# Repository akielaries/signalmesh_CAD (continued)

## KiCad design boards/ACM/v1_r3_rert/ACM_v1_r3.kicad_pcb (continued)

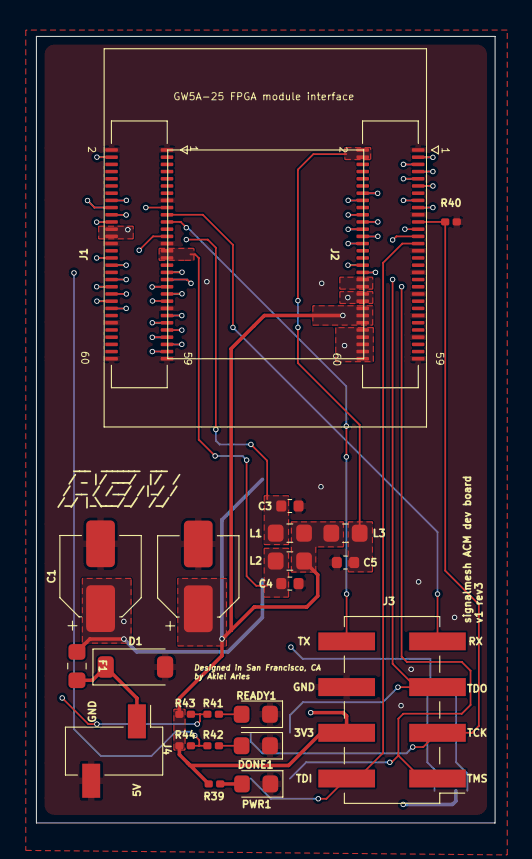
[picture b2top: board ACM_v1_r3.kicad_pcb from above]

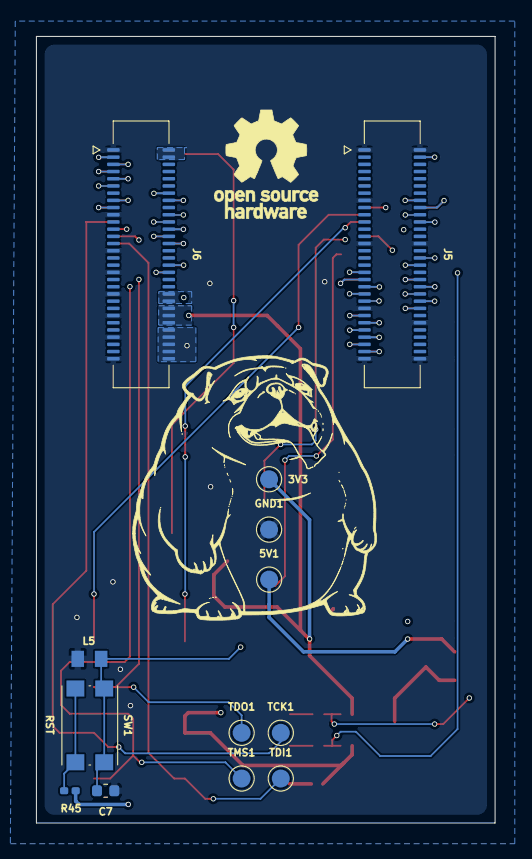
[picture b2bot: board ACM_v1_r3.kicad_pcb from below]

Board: 4 copper layers, 25.5 x 43.7 mm, 36 parts (13 on the bottom side), 66 nets.

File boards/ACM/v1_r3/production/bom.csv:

Designator,Footprint,Quantity,Value,LCSC Part #
"3V3, 5V1, GND1, TCK1, TDI1, TDO1, TMS1",TestPoint_Pad_D1.0mm,7,TestPoint,
"C1, C2",CP_Elec_4x3,2,220uF 10V,
"C3, C4, C5, C7",0402,4,100nF,
D1,D_SOD-123,1,20V 3A,
"DONE1, PWR1, READY1",0603,3,GREEN_LED,
F1,0603,1,6V 2A,
"J1, J2, J5, J6",Hirose_DF40C-60DS-0.4V_2x30_P0.4mm,4,DF40C-60DS-0.4V(51),
J3,PinHeader_2x04_P2.54mm_Vertical_SMD,1,Conn_02x04_Odd_Even,
J4,PinSocket_1x02_P2.54mm_Vertical_SMD_Pin1Left,1,Conn_01x02,
"L1, L2, L3",0603,3,PZ1608D300-3R0TF,
L5,INDC1005X45,1,LXES15AAA1-153,
"R39, R41, R42",0201,3,4.7k,
R40,0201,1,5.1K,
"R43, R44",0201,2,49.9k,
R45,0201,1,100R,
SW1,SW_Push_1P1T_NO_CK_KMR2,1,RST,

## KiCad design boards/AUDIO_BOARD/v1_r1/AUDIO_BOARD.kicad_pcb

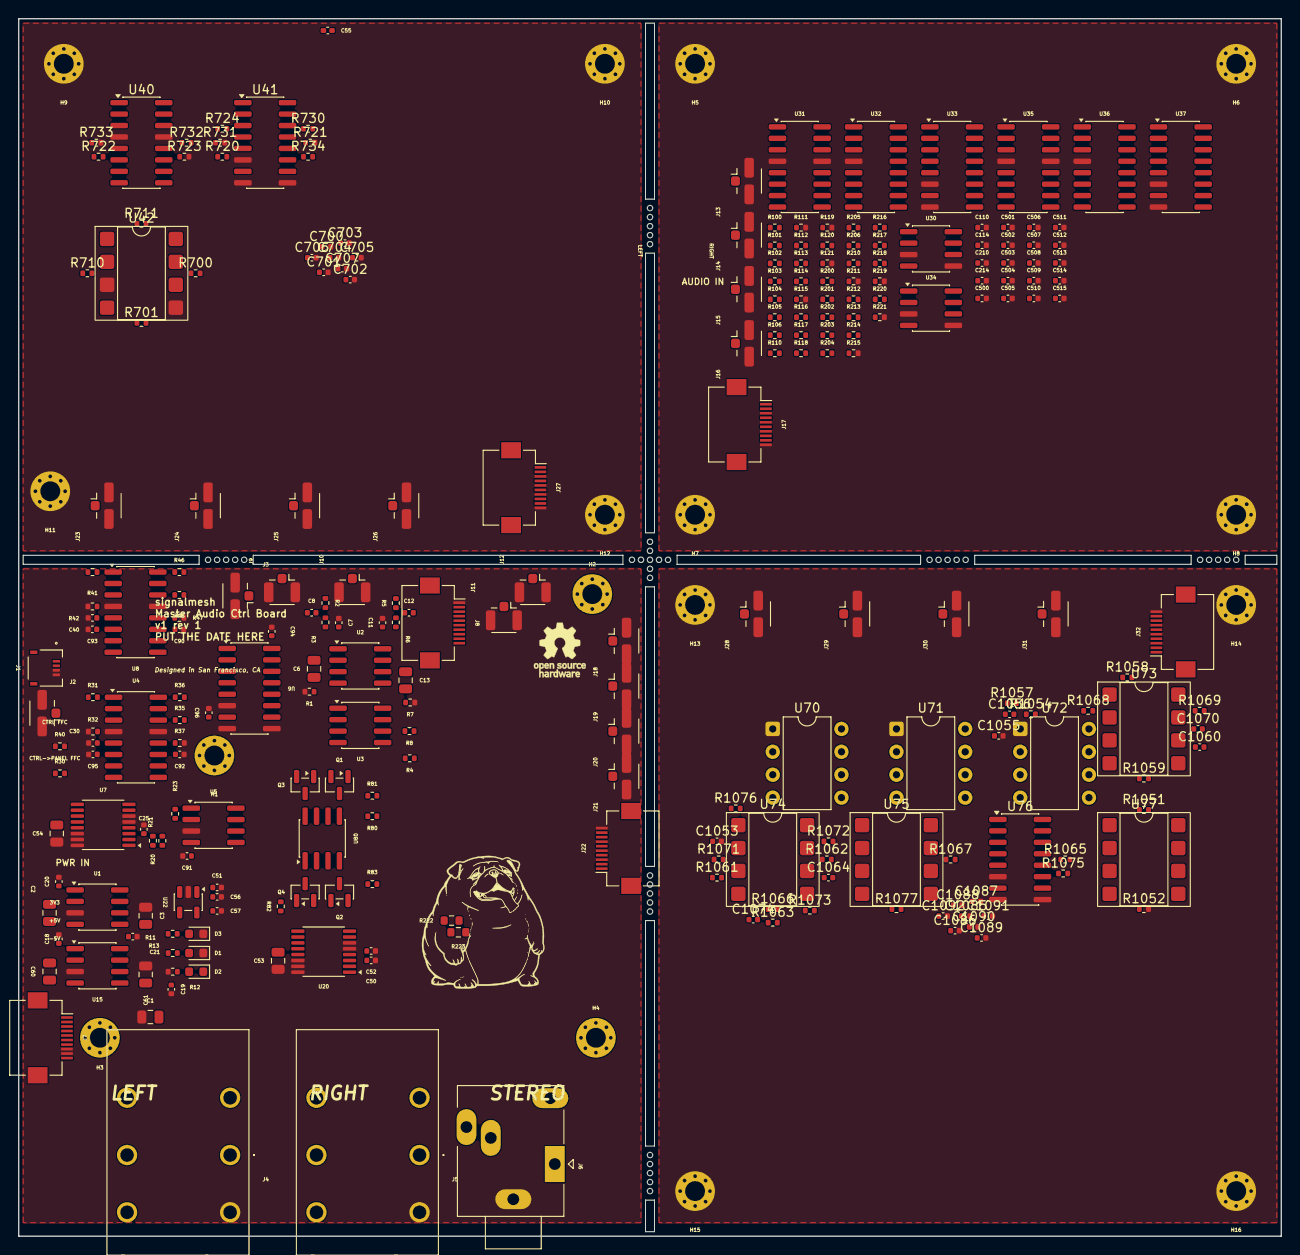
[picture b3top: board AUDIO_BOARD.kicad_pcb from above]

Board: 4 copper layers, 140.0 x 135.0 mm, 266 parts (0 on the bottom side), 170 nets, no tracks yet.

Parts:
C1, C2, C3, C53, C54: 10uF; C_0805_2012Metric
C6, C13, C60: 1uF; C_0805_2012Metric
C7, C11: 560pF; C_0402_1005Metric
C8, C12, C30, C40, C110, C114, C210, C214, C1060, C1064, C1070, C1074: 1nF; C_0402_1005Metric
C18, C19, C20, C21, C51, C52, C55, C90, C91, C92, C93, C94, C95, C96, C500, C501, C502, C503, C504, C505, C506, C507, C508, C509, C510, C511, C512, C513, C514, C515, C700, C701, C702, C703, C704, C705, C706, C707, C1085, C1086, C1087, C1088, C1089, C1090, C1091, C1092: 100nF; C_0402_1005Metric
C25, C50, C56, C57: 1uF; C_0402_1005Metric
C61: 22uF; C_0805_2012Metric
C1053: 10uF; C_0402_1005Metric
C1055, C1056: 100pF; C_0402_1005Metric
D1, D2, D3: LED; LED_0603_1608Metric
H1, H2, H3, H4, H5, H6, H7, H8, H9, H10, H11, H12, H13, H14, H15, H16: M2; MountingHole_2.2mm_M2_Pad_Via
J1: PWR FFC 4p; AMPHENOL_F3311A7H121004E200
J2: U.FL L in; U.FL_Hirose_U.FL-R-SMT-1_Vertical
J3: U.FL R in; U.FL_Hirose_U.FL-R-SMT-1_Vertical
J4: 1/4in L; ACJSMHOM
J5: 1/4in R; ACJSMHOM
J6: 3.5mm HP; Jack_3.5mm_Ledino_KB3SPRS_Horizontal
J7: CTRL FFC; Hirose_FH12-10S-0.5SH_1x10-1MP_P0.50mm_Horizontal
J8: CTRL->PANEL FFC; Hirose_FH12-10S-0.5SH_1x10-1MP_P0.50mm_Horizontal
J9: U.FL FX send L; U.FL_Hirose_U.FL-R-SMT-1_Vertical
J10: U.FL FX send R; U.FL_Hirose_U.FL-R-SMT-1_Vertical
J11: U.FL FX return L; U.FL_Hirose_U.FL-R-SMT-1_Vertical
J12: U.FL FX return R; U.FL_Hirose_U.FL-R-SMT-1_Vertical
J13: U.FL AUDIO L IN; U.FL_Hirose_U.FL-R-SMT-1_Vertical
J14: U.FL AUDIO R IN; U.FL_Hirose_U.FL-R-SMT-1_Vertical
J15: U.FL AUDIO L OUT; U.FL_Hirose_U.FL-R-SMT-1_Vertical
J16: U.FL AUDIO R OUT; U.FL_Hirose_U.FL-R-SMT-1_Vertical
J17: FILTER FFC; Hirose_FH12-10S-0.5SH_1x10-1MP_P0.50mm_Horizontal
J18: U.FL->FILT L IN; U.FL_Hirose_U.FL-R-SMT-1_Vertical
J19: U.FL->FILT R IN; U.FL_Hirose_U.FL-R-SMT-1_Vertical
J20: U.FL<-FILT L OUT; U.FL_Hirose_U.FL-R-SMT-1_Vertical
J21: U.FL<-FILT R OUT; U.FL_Hirose_U.FL-R-SMT-1_Vertical
J22: FILTER-IF FFC; Hirose_FH12-10S-0.5SH_1x10-1MP_P0.50mm_Horizontal
J23: FX-A L IN; U.FL_Hirose_U.FL-R-SMT-1_Vertical
J24: FX-A R IN; U.FL_Hirose_U.FL-R-SMT-1_Vertical
J25: FX-A L OUT; U.FL_Hirose_U.FL-R-SMT-1_Vertical
J26: FX-A R OUT; U.FL_Hirose_U.FL-R-SMT-1_Vertical
J27: FX-A CTRL; Hirose_FH12-10S-0.5SH_1x10-1MP_P0.50mm_Horizontal
J28: FX-B L IN; U.FL_Hirose_U.FL-R-SMT-1_Vertical
J29: FX-B R IN; U.FL_Hirose_U.FL-R-SMT-1_Vertical
J30: FX-B L OUT; U.FL_Hirose_U.FL-R-SMT-1_Vertical
J31: FX-B R OUT; U.FL_Hirose_U.FL-R-SMT-1_Vertical
J32: FX-B CTRL; Hirose_FH12-10S-0.5SH_1x10-1MP_P0.50mm_Horizontal
Q1, Q3: MMBT3904; SOT-23
Q2, Q4: MMBT3906; SOT-23
R1, R7, R20, R21, R23, R31, R36, R41, R46, R100, R101, R102, R103, R104, R105, R106, R112, R116, R120, R200, R201, R202, R203, R204, R205, R206, R212, R216, R220, R722, R732, R1051, R1052: 100k; R_0402_1005Metric
R2, R3, R5, R6, R113, R117, R213, R217, R724, R734, R1058, R1059, R1061, R1062, R1063, R1068, R1069, R1071, R1072, R1073: 10k; R_0402_1005Metric
R4, R8, R80, R82: 100R; R_0402_1005Metric
R11, R12, R13: 1k; R_0402_1005Metric
R30, R35, R40, R45: 20k; R_0402_1005Metric
R32, R37, R42, R47, R121, R221, R701, R711, R723, R733, R1054: 47k; R_0402_1005Metric
R81, R83: 22R; R_0402_1005Metric
R110, R114, R118, R210, R214, R218, R720, R730, R1065, R1066, R1067, R1075, R1076, R1077: 22k; R_0402_1005Metric
R111, R115, R119, R211, R215, R219, R721, R731: 220R; R_0402_1005Metric
R222, R223: 0; R_0603_1608Metric
R700, R710: 4k7; R_0402_1005Metric
R1057: 220k; R_0402_1005Metric
U1, U15: LTC660; SOIC-8_3.9x4.9mm_P1.27mm
U2, U3, U5, U30, U34, U80: OPA1678; SOIC-8_3.9x4.9mm_P1.27mm
U4, U8, U31, U32, U35, U36, U40: LM13700; SOIC-16_3.9x9.9mm_P1.27mm
U6, U41, U76: 4053; SOIC-16_3.9x9.9mm_P1.27mm
U7, U20: DAC8565; TSSOP-16_4.4x5mm_P0.65mm
U22: AP2112K-3.3; SOT-23-5
U33, U37: 4052; SOIC-16_3.9x9.9mm_P1.27mm
U42, U73, U74, U75, U77: OPA1678; DIP-8_W7.62mm_SMDSocket_SmallPads
U70, U71: MN3207; DIP-8_W7.62mm
U72: MN3101; DIP-8_W7.62mm

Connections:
+3V3: C55.1, C57.1, J8.8, R13.1, U22.5 (VOUT)
+5V: C1.1, C18.1, C20.1, C51.1, C52.1, C53.1, C54.1, C56.1, C90.1, C92.1, C94.1, J1.1, J1.2, J22.1, Q1.3 (C), Q3.3 (C), R11.1, U1.1 (BOOST), U1.8 (V+), U2.8 (V+), U3.8 (V+), U4.11 (V+), U5.8 (V+), U6.16 (VDD), U7.4 (AVDD), U7.12 (IOVDD), U7.13 (~RST), U8.11 (V+), U15.1 (BOOST), U15.8 (V+), U20.4 (AVDD), U20.12 (IOVDD), U20.13 (~RST), U22.1 (VIN), U22.3 (EN), U80.8 (V+)
-5V: C3.1, C19.1, C21.1, C61.1, C91.1, C93.1, C95.1, C96.1, D2.1 (K), J22.2, Q2.3 (C), Q4.3 (C), U1.5 (VOUT), U2.4 (V-), U3.4 (V-), U4.6 (V-), U5.4 (V-), U6.7 (VEE), U8.6 (V-), U15.5 (VOUT), U80.4 (V-)
/ANALOG_FILTER_CV/CV_CUTOFF: R20.2, U7.1 (VOUTA)
/ANALOG_FILTER_CV/CV_VCA: R36.2, R46.2, U7.7 (VOUTC)
/ANALOG_FILTER_CV/VCA_L_OUT: R37.1, U4.12, U6.13 (X1)
/ANALOG_FILTER_CV/VCA_R_OUT: R47.1, U6.1 (Y1), U8.12
/ANALOG_FILTER_CV/VCF_L_OUT: C30.1, R32.1, R35.1, U4.5
/ANALOG_FILTER_CV/VCF_R_OUT: C40.1, R42.1, R45.1, U8.5
/ANALOG_FILTER_CV/VCUTOFF: R23.2, R31.2, R41.2, U5.1
/ANALOG_FILTER_CV/VREF: C25.1, U7.3 (VREFH/VREFOUT)
/CS_DAC1: J7.4, U7.9 (~SYNC)
/CS_DAC2: J7.10, U20.9 (~SYNC)
/CS_POTS: J7.5, J8.5
/FILT_L_IN: R4.2, R30.2, U6.12 (X0)
/FILT_L_OUT: J9.1 (In), R222.2, U6.14 (X)
/FILT_R_IN: R8.2, R40.1, U6.2 (Y0)
/FILT_R_OUT: J10.1 (In), R223.2, U6.15 (Y)
/FX_CHAIN/DRV_L: R701.2, R720.1, R721.1, U41.12, U42.1
/FX_CHAIN/DRV_R: R711.2, R730.1, R731.1, U41.2, U42.7
/FX_CHAIN/TREM_L: R724.1, U40.8, U41.13
/FX_CHAIN/TREM_R: R734.1, U40.9, U41.1
/FX_CHORUS/AA_L: C1060.1, R1059.1, U70.3, U73.1
/FX_CHORUS/AA_R: C1070.1, R1069.1, U71.3, U73.7
/FX_CHORUS/BO1_L: R1061.1, U70.7
/FX_CHORUS/BO1_R: R1071.1, U71.7
/FX_CHORUS/BO2_L: R1062.1, U70.8
/FX_CHORUS/BO2_R: R1072.1, U71.8
/FX_CHORUS/CHW_L: R1067.1, U75.1, U76.13
/FX_CHORUS/CHW_R: R1077.1, U75.7, U76.1
/FX_CHORUS/CH_L_IN: R1065.1, U76.12
/FX_CHORUS/CH_R_IN: R1075.1, U76.2
/FX_CHORUS/CLK1: U70.2, U71.2, U72.2
/FX_CHORUS/CLK2: U70.6, U71.6, U72.4
/FX_CHORUS/GND: U75.3, U75.5
/FX_CHORUS/IL_L: C1060.2, R1058.2, R1059.2, U73.2
/FX_CHORUS/IL_R: C1070.2, R1068.2, R1069.2, U73.6
/FX_CHORUS/ML_L: R1065.2, R1066.2, R1067.2, U75.2
/FX_CHORUS/ML_R: R1075.2, R1076.2, R1077.2, U75.6
/FX_CHORUS/OL_L: C1064.2, R1061.2, R1062.2, R1063.2, U74.2
/FX_CHORUS/OL_R: C1074.2, R1071.2, R1072.2, R1073.2, U74.6
/FX_CHORUS/OSC1: R1054.1, R1057.2, U72.7
/FX_CHORUS/OSC2: C1056.1, R1054.2, U72.6
/FX_CHORUS/OSC3: C1055.1, C1056.2, U72.5
/FX_CHORUS/VGGB: U70.4, U71.4, U72.8
/FX_CHORUS/VMID: C1053.1, U73.3, U73.5, U74.3, U74.5, U77.1, U77.2
/FX_CHORUS/VMIDR: R1051.2, R1052.1, U77.3
/FX_CHORUS/WET_L: C1064.1, R1063.1, R1066.1, U74.1
/FX_CHORUS/WET_R: C1074.1, R1073.1, R1076.1, U74.7
/FX_CONTROL/VREF2: C50.1, U20.3 (VREFH/VREFOUT)
/FX_RET_L: J11.1 (In), J18.1 (In), R222.1
/FX_RET_R: J12.1 (In), J19.1 (In), R223.1
/GATE: J7.7, J8.9
/HP_L: J6.T, R81.2
/HP_R: J6.R, R83.2
/LINE_L: J4.T1, R80.2
/LINE_R: J5.T1, R82.2
/MASTER_FILTER/AUDIO_L_IN: J13.1 (In), R100.1
/MASTER_FILTER/AUDIO_L_OUT: J15.1 (In), U33.13 (X)
/MASTER_FILTER/AUDIO_R_IN: J14.1 (In), R200.1
/MASTER_FILTER/AUDIO_R_OUT: J16.1 (In), U37.13 (X)
/MASTER_FILTER/BPL: R113.1, R114.1, R115.1, R118.1, R119.1, U31.8, U33.14 (X1)
/MASTER_FILTER/BPR: R213.1, R214.1, R215.1, R218.1, R219.1, U35.8, U37.14 (X1)
/MASTER_FILTER/CV_CUTOFF: J17.4, R112.2, R116.2, R212.2, R216.2
/MASTER_FILTER/CV_RES: J17.6, R120.2, R220.2
/MASTER_FILTER/HPL: R103.2, R104.1, R110.1, R111.1, U30.1, U33.15 (X2)
/MASTER_FILTER/HPR: R203.2, R204.1, R210.1, R211.1, U34.1, U37.15 (X2)
/MASTER_FILTER/LPL: R101.1, R105.1, R117.1, U31.9, U33.12 (X0)
/MASTER_FILTER/LPR: R201.1, R205.1, R217.1, U35.9, U37.12 (X0)
/MASTER_FILTER/MODE_A: J17.8, U33.10 (A), U37.10 (A)
/MASTER_FILTER/MODE_B: J17.9, U33.9 (B), U37.9 (B)
/MASTER_FILTER/NOTCHL: R106.2, U30.7, U33.11 (X3)
/MASTER_FILTER/NOTCHR: R206.2, U34.7, U37.11 (X3)
/MASTER_FILTER/RESFBL: R102.1, U32.8
/MASTER_FILTER/RESFBR: R202.1, U36.8
/MF_CV_CUTOFF: J22.4, U20.1 (VOUTA)
/MF_CV_RES: J22.6, U20.2 (VOUTB)
/MF_MODE_A: J8.6, J22.8
/MF_MODE_B: J8.7, J22.9
/MODE_SEL: J7.6, U6.10 (B), U6.11 (A)
/OUTPUT_BUF/BUF_L: Q1.2 (E), Q2.2 (E), R80.1, R81.1, U80.2 (-)
/OUTPUT_BUF/BUF_R: Q3.2 (E), Q4.2 (E), R82.1, R83.1, U80.6 (-)
/SPI_MISO: J7.3, J8.4
/SPI_MOSI: J7.2, J8.3, U7.11 (DIN), U20.11 (DIN)
/SPI_SCK: J7.1, J8.2, U7.10 (SCLK), U20.10 (SCLK)
/VOL_L: J20.1 (In), U80.3 (+)
/VOL_R: J21.1 (In), U80.5 (+)
CV_MOD: R21.1, U20.7 (VOUTC)
FILT_+5V: C500.1, C502.1, C504.1, C506.1, C508.1, C510.1, C512.1, C514.1, J17.1, U30.8 (V+), U31.11 (V+), U32.11 (V+), U33.16 (VDD), U34.8 (V+), U35.11 (V+), U36.11 (V+), U37.16 (VDD)
FILT_-5V: C501.1, C503.1, C505.1, C507.1, C509.1, C511.1, C513.1, C515.1, J17.2, R113.2, R117.2, R213.2, R217.2, U30.4 (V-), U31.6 (V-), U32.6 (V-), U33.7 (VEE), U34.4 (V-), U35.6 (V-), U36.6 (V-), U37.7 (VEE)
FILT_GND: C110.2, C114.2, C210.2, C214.2, C500.2, C501.2, C502.2, C503.2, C504.2, C505.2, C506.2, C507.2, C508.2, C509.2, C510.2, C511.2, C512.2, C513.2, C514.2, C515.2, H5.1, H6.1, H7.1, H8.1, J13.2 (Ext), J14.2 (Ext), J15.2 (Ext), J16.2 (Ext), J17.3, J17.5, J17.7, J17.10, R111.2, R115.2, R119.2, R121.2, R211.2, R215.2, R219.2, R221.2, U30.3 (+), U30.5 (+), U31.4 (-), U31.13 (-), U32.4 (-), U33.6 (Inh), U33.8 (VSS), U34.3 (+), U34.5 (+), U35.4 (-), U35.13 (-), U36.4 (-), U37.6 (Inh), U37.8 (VSS)
FXA_+5V: C700.1, C702.1, C704.1, C706.1, J27.1, U40.11, U41.16, U42.8
FXA_-5V: C701.1, C703.1, C705.1, C707.1, J27.2, R724.2, R734.2, U40.6, U41.7, U42.4
FXA_CV1: J27.4, R722.2, R732.2
FXA_D1: J27.8, U41.10, U41.11
FXA_GND: C700.2, C701.2, C702.2, C703.2, C704.2, C705.2, C706.2, C707.2, H9.1, H10.1, H11.1, H12.1, J23.2 (Ext), J24.2 (Ext), J25.2 (Ext), J26.2 (Ext), J27.3, J27.5, J27.7, J27.10, R721.2, R723.2, R731.2, R733.2, U40.4, U40.13, U41.6, U41.8, U41.9, U42.3, U42.5
FXA_L_IN: J23.1 (In), R700.1
FXA_L_OUT: J25.1 (In), U41.14
FXA_R_IN: J24.1 (In), R710.1
FXA_R_OUT: J26.1 (In), U41.15
FXB_+5V: C1085.1, C1087.1, C1089.1, C1091.1, J32.1, R1051.1, U70.5, U71.5, U72.3, U73.8, U74.8, U75.8, U76.16, U77.8
FXB_-5V: C1086.1, C1088.1, C1090.1, C1092.1, J32.2, U73.4, U74.4, U75.4, U76.7, U77.4
FXB_CV1: J32.4, R1057.1
FXB_D1: J32.8, U76.11
FXB_GND: C1053.2, C1055.2, C1085.2, C1086.2, C1087.2, C1088.2, C1089.2, C1090.2, C1091.2, C1092.2, H13.1, H14.1, H15.1, H16.1, J28.2 (Ext), J29.2 (Ext), J30.2 (Ext), J31.2 (Ext), J32.3, J32.5, J32.7, J32.10, R1052.2, U70.1, U71.1, U72.1, U76.6, U76.8, U76.9
FXB_L_IN: J28.1 (In), R1058.1
FXB_L_OUT: J30.1 (In), U76.14
FXB_R_IN: J29.1 (In), R1068.1
FXB_R_OUT: J31.1 (In), U76.15
GND: C1.2, C3.2, C7.1, C11.1, C18.2, C19.2, C20.2, C21.2, C25.2, C30.2, C40.2, C50.2, C51.2, C52.2, C53.2, C54.2, C55.2, C56.2, C57.2, C61.2, C90.2, C91.2, C92.2, C93.2, C94.2, C95.2, C96.2, D1.1 (K), D3.1 (K), J1.3, J1.4, J2.2 (Ext), J3.2 (Ext), J4.S1, J5.S1, J6.S, J7.8, J7.9, J8.1, J9.2 (Ext), J10.2 (Ext), J11.2 (Ext), J12.2 (Ext), J18.2 (Ext), J19.2 (Ext), J20.2 (Ext), J21.2 (Ext), J22.3, J22.5, J22.7, J22.10, R1.2, R7.2, R12.1, R32.2, R37.2, R42.2, R47.2, U1.3 (GND), U4.4 (-), U4.13 (-), U5.3 (+), U6.6 (Inh), U6.8 (VSS), U6.9 (C), U7.5 (VREFL), U7.6 (GND), U7.14 (RSTSEL), U7.15 (~ENABLE), U7.16 (LDAC), U8.4 (-), U8.13 (-), U15.3 (GND), U20.5 (VREFL), U20.6 (GND), U20.14 (RSTSEL), U20.15 (~ENABLE), U20.16 (LDAC), U22.2 (GND)
unnamed: C8.1, R2.2, R3.1
unnamed: C12.1, R5.2, R6.1
unnamed: C110.1, U31.5, U31.7
unnamed: C114.1, U31.10, U31.12
unnamed: C210.1, U35.5, U35.7
unnamed: C214.1, U35.10, U35.12
unnamed: D1.2 (A), R11.2
unnamed: D2.2 (A), R12.2
unnamed: D3.2 (A), R13.2
unnamed: J2.1 (In), R2.1
unnamed: J3.1 (In), R5.1
unnamed: Q1.1 (B), Q2.1 (B), U80.1
unnamed: Q3.1 (B), Q4.1 (B), U80.7
unnamed: R31.1, U4.1
unnamed: R36.1, U4.16
unnamed: R41.1, U8.1
unnamed: R46.1, U8.16
unnamed: R112.1, U31.1
unnamed: R116.1, U31.16
unnamed: R120.1, U32.1
unnamed: R121.1, U32.5, U32.7
unnamed: R212.1, U35.1
unnamed: R216.1, U35.16
unnamed: R220.1, U36.1
unnamed: R221.1, U36.5, U36.7
unnamed: R722.1, U40.1
unnamed: R723.1, U40.5, U40.7
unnamed: R732.1, U40.16
unnamed: R733.1, U40.10, U40.12
unnamed: C2.1, U1.2 (CAP+)
unnamed: C2.2, U1.4 (CAP-)
unnamed: C7.2, R3.2, U2.3 (+)
unnamed: C6.1, C8.2, U2.1, U2.2 (-)
unnamed: C11.2, R6.2, U2.5 (+)
unnamed: C12.2, C13.1, U2.6 (-), U2.7
unnamed: C6.2, R1.1, U3.3 (+)
unnamed: R4.1, U3.1, U3.2 (-)
unnamed: C13.2, R7.1, U3.5 (+)
unnamed: R8.1, U3.6 (-), U3.7
unnamed: R35.2, U4.14 (+)
unnamed: R30.1, U4.3 (+)
unnamed: R20.1, R21.2, R23.1, U5.2 (-)
unnamed: R45.2, U8.14 (+)
unnamed: R40.2, U8.3 (+)
unnamed: C60.1, U15.2 (CAP+)
unnamed: C60.2, U15.4 (CAP-)
unnamed: R100.2, R101.2, R102.2, R103.1, U30.2 (-)
unnamed: R104.2, R105.2, R106.1, U30.6 (-)
unnamed: R114.2, U31.14 (+)
unnamed: R110.2, U31.3 (+)
unnamed: R118.2, U32.3 (+)
unnamed: R200.2, R201.2, R202.2, R203.1, U34.2 (-)
unnamed: R204.2, R205.2, R206.1, U34.6 (-)
unnamed: R214.2, U35.14 (+)
unnamed: R210.2, U35.3 (+)
unnamed: R218.2, U36.3 (+)
unnamed: R730.2, U40.14
unnamed: R720.2, U40.3
unnamed: R700.2, R701.1, U42.2
unnamed: R710.2, R711.1, U42.6

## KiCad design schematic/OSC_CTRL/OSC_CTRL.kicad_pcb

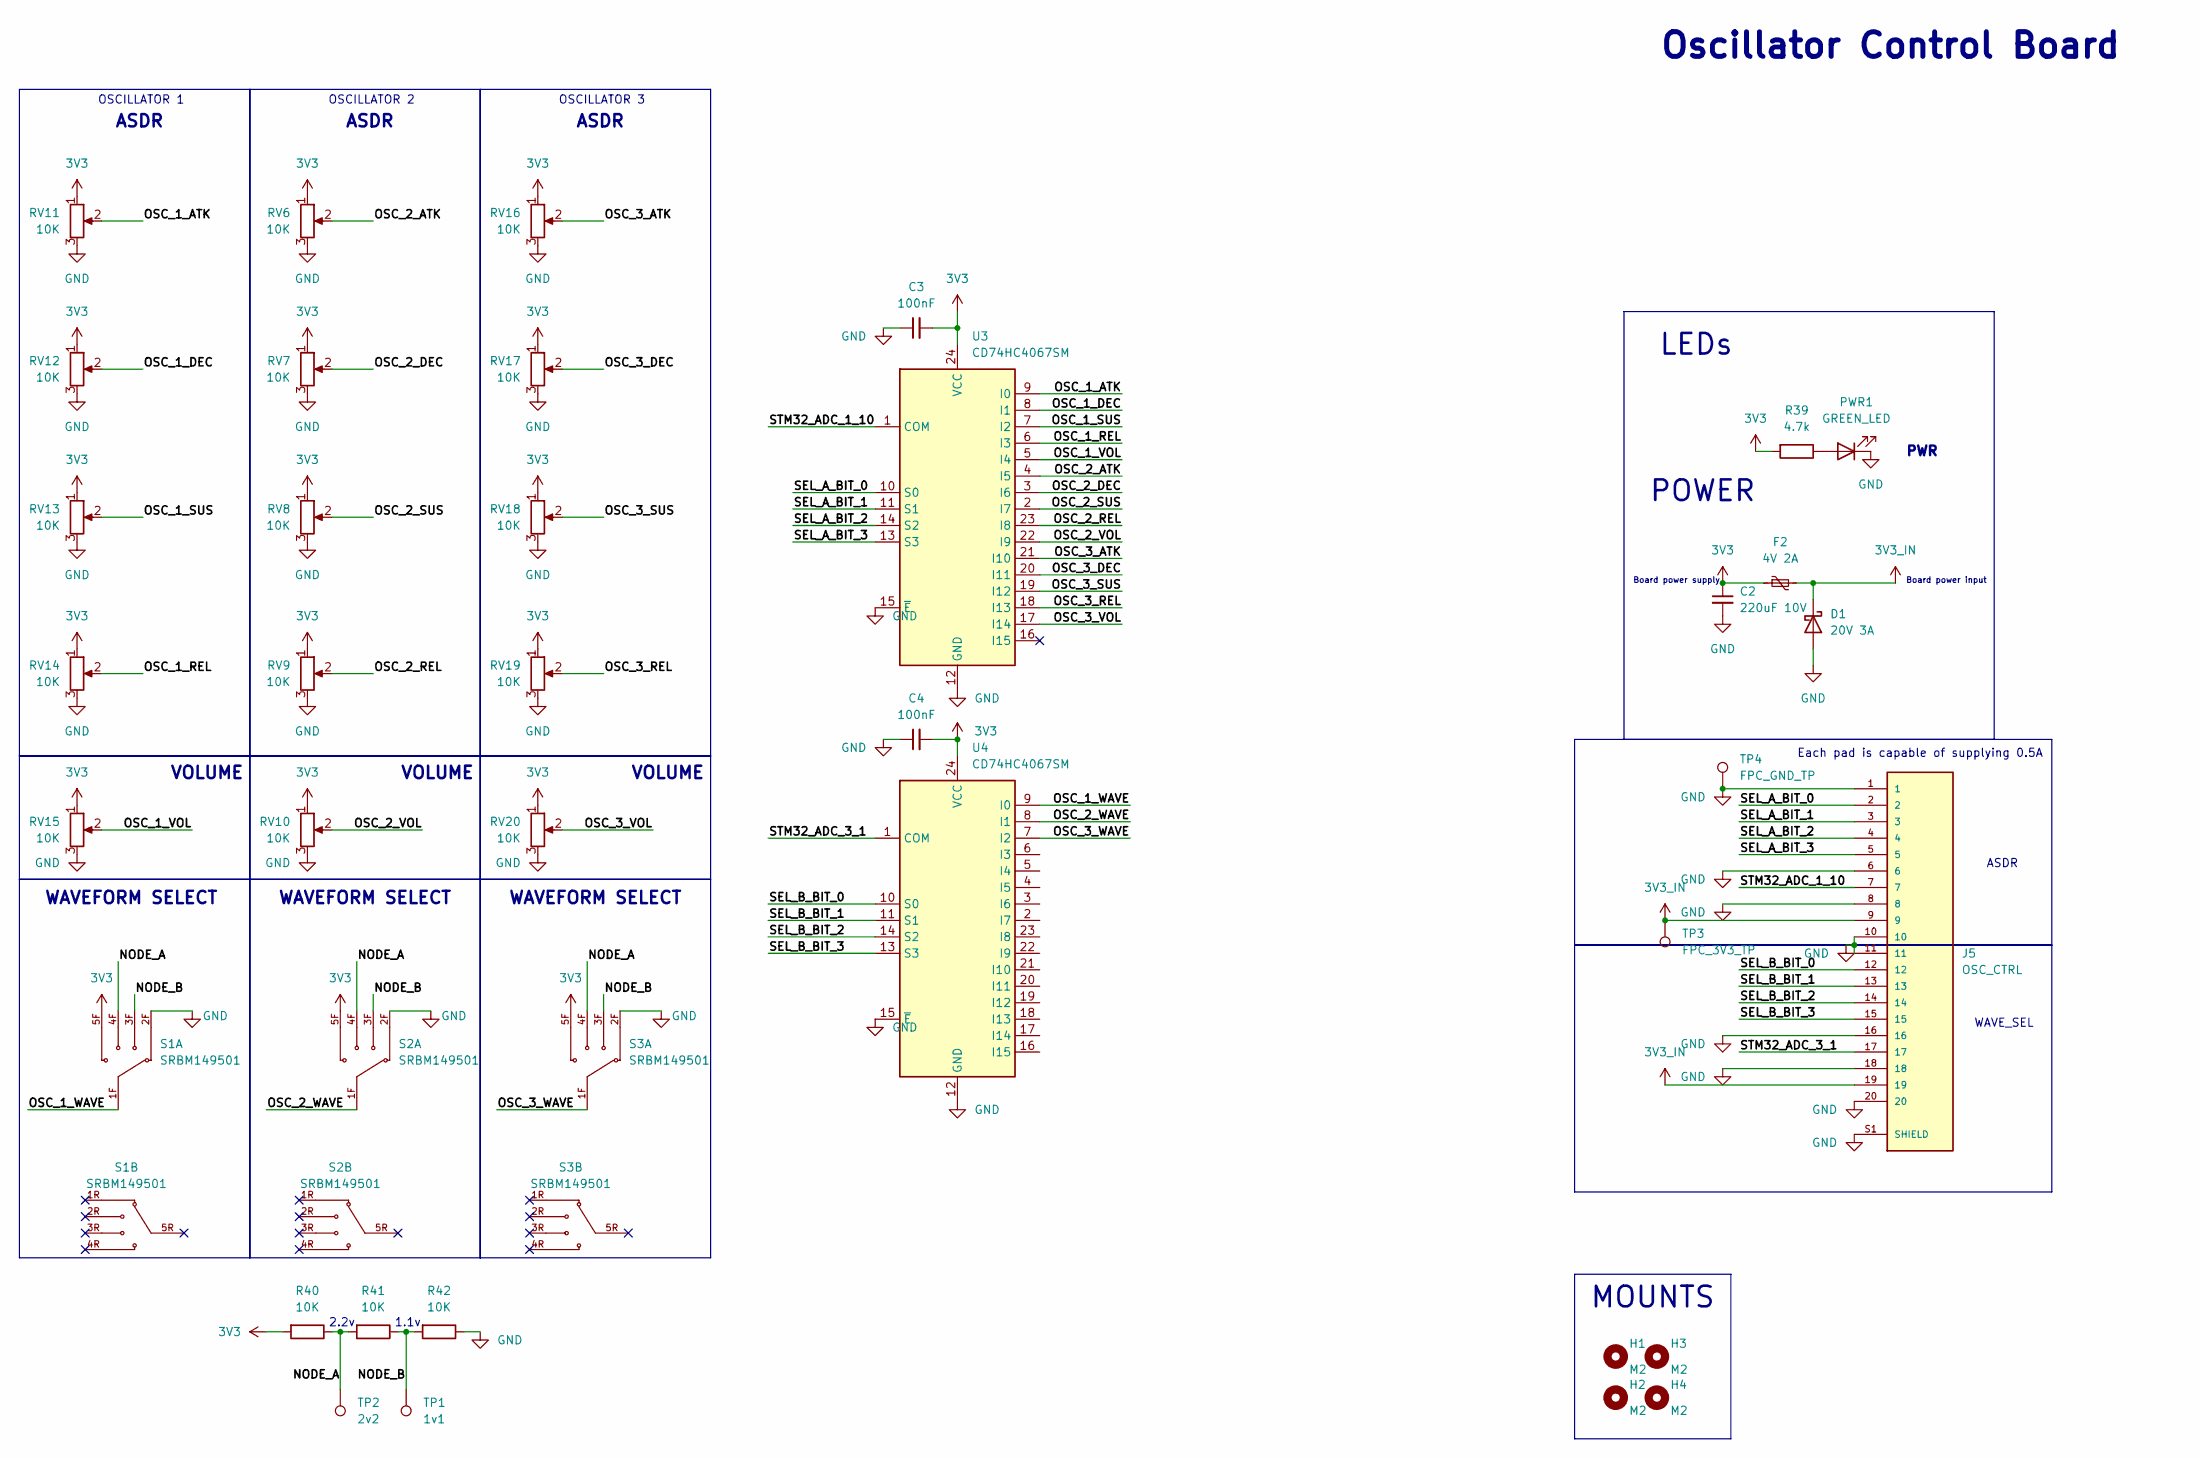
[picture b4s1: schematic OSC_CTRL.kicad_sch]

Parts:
C2: 220uF 10V; CP_Elec_4x3
C3, C4: 100nF; C_0402_1005Metric
D1: 20V 3A; D_SOD-123
F2: 4V 2A; Fuse_0603_1608Metric
H1, H2, H3, H4: M2; MountingHole_2.2mm_M2_Pad_Via
J5: OSC_CTRL; GCT_FFC2B28-20-G; PARTREV A
PWR1: GREEN_LED; LED_0603_1608Metric
R39: 4.7k; R_0201_0603Metric; DigiKey_Part_Number 311-10.0KCRCT-ND
R40, R41, R42: 10K; R_0201_0603Metric; DigiKey_Part_Number 311-10.0KCRCT-ND
RV6, RV7, RV8, RV9, RV11, RV12, RV13, RV14, RV16, RV17, RV18, RV19: 10K; Potentiometer_Bourns_PTA4543_Single_Slide
RV10, RV15, RV20: 10K; Potentiometer_Piher_PC-16_Single_Horizontal
S1, S2, S3: SRBM149501; SW_SRBM149501; PARTREV N/A
TP1: 1v1; TestPoint_Pad_D1.0mm
TP2: 2v2; TestPoint_Pad_D1.0mm
TP3: FPC_3V3_TP; TestPoint_Pad_D1.0mm
TP4: FPC_GND_TP; TestPoint_Pad_D1.0mm
U3, U4: CD74HC4067SM; SSOP-24_5.3x8.2mm_P0.65mm

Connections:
3V3: C2.1, C3.2, C4.2, F2.1, R39.2, R40.2, RV6.1, RV7.1, RV8.1, RV9.1, RV10.1, RV11.1, RV12.1, RV13.1, RV14.1, RV15.1, RV16.1, RV17.1, RV18.1, RV19.1, RV20.1, S1.5F, S2.5F, S3.5F, U3.24 (VCC), U4.24 (VCC)
3V3_IN: D1.1 (K), F2.2, J5.9, J5.19, TP3.1 (1_1)
/NODE_A: R40.1, R41.2, S1.4F, S2.4F, S3.4F, TP2.1 (1_1)
/NODE_B: R41.1, R42.2, S1.3F, S2.3F, S3.3F, TP1.1 (1_1)
/OSC_1_ATK: RV11.2, U3.9 (I0)
/OSC_1_DEC: RV12.2, U3.8 (I1)
/OSC_1_REL: RV14.2, U3.6 (I3)
/OSC_1_SUS: RV13.2, U3.7 (I2)
/OSC_1_VOL: RV15.2, U3.5 (I4)
/OSC_1_WAVE: S1.1F, U4.9 (I0)
/OSC_2_ATK: RV6.2, U3.4 (I5)
/OSC_2_DEC: RV7.2, U3.3 (I6)
/OSC_2_REL: RV9.2, U3.23 (I8)
/OSC_2_SUS: RV8.2, U3.2 (I7)
/OSC_2_VOL: RV10.2, U3.22 (I9)
/OSC_2_WAVE: S2.1F, U4.8 (I1)
/OSC_3_ATK: RV16.2, U3.21 (I10)
/OSC_3_DEC: RV17.2, U3.20 (I11)
/OSC_3_REL: RV19.2, U3.18 (I13)
/OSC_3_SUS: RV18.2, U3.19 (I12)
/OSC_3_VOL: RV20.2, U3.17 (I14)
/OSC_3_WAVE: S3.1F, U4.7 (I2)
/SEL_A_BIT_0: J5.2, U3.10 (S0)
/SEL_A_BIT_1: J5.3, U3.11 (S1)
/SEL_A_BIT_2: J5.4, U3.14 (S2)
/SEL_A_BIT_3: J5.5, U3.13 (S3)
/SEL_B_BIT_0: J5.12, U4.10 (S0)
/SEL_B_BIT_1: J5.13, U4.11 (S1)
/SEL_B_BIT_2: J5.14, U4.14 (S2)
/SEL_B_BIT_3: J5.15, U4.13 (S3)
/STM32_ADC_1_10: J5.7, U3.1 (COM)
/STM32_ADC_3_1: J5.17, U4.1 (COM)
GND: C2.2, C3.1, C4.1, D1.2 (A), J5.1, J5.6, J5.8, J5.10, J5.11, J5.16, J5.18, J5.20, J5.S1 (SHIELD), J5.S2 (SHIELD), PWR1.1 (K), R42.1, RV6.3, RV7.3, RV8.3, RV9.3, RV10.3, RV11.3, RV12.3, RV13.3, RV14.3, RV15.3, RV16.3, RV17.3, RV18.3, RV19.3, RV20.3, S1.2F, S2.2F, S3.2F, TP4.1 (1_1), U3.12 (GND), U3.15 (~E), U4.12 (GND), U4.15 (~E)
unnamed: PWR1.2 (A), R39.1

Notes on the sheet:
2.2v
Board power supply
1.1v
ASDR
VOLUME
Oscillator Control Board
WAVEFORM SELECT
OSCILLATOR 2
POWER
OSCILLATOR 3
Each pad is capable of supplying 0.5A
Board power input
MOUNTS
WAVE_SEL
LEDs
PWR
OSCILLATOR 1

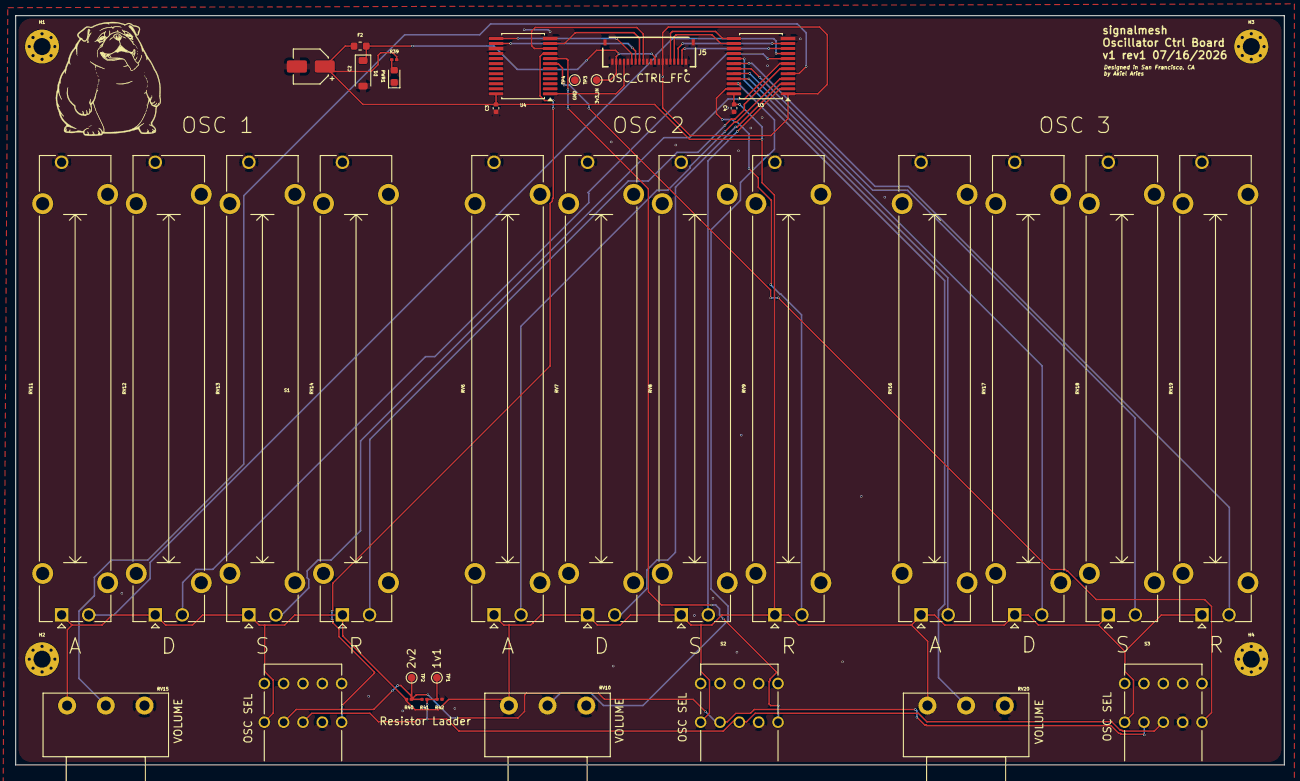
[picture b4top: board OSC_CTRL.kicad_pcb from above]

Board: 2 copper layers, 164.0 x 96.8 mm, 39 parts (0 on the bottom side), 34 nets.

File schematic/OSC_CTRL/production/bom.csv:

Designator,Footprint,Quantity,Value,LCSC Part #
C2,CP_Elec_4x3,1,220uF 10V,
"C3, C4",0402,2,100nF,
D1,D_SOD-123,1,20V 3A,
F2,0603,1,4V 2A,
"H1, H2, H3, H4",MountingHole_2.2mm_M2_Pad_Via,4,M2,
J5,GCT_FFC2B28-20-G,1,OSC_CTRL,
PWR1,0603,1,GREEN_LED,
R39,0201,1,4.7k,
"R40, R41, R42",0201,3,10K,
"RV10, RV15, RV20",Potentiometer_Piher_PC-16_Single_Horizontal,3,10K,
"RV11, RV12, RV13, RV14, RV16, RV17, RV18, RV19, RV6, RV7, RV8, RV9",Potentiometer_Bourns_PTA4543_Single_Slide,12,10K,
"S1, S2, S3",SW_SRBM149501,3,SRBM149501,
TP1,TestPoint_Pad_D1.0mm,1,1v1,
TP2,TestPoint_Pad_D1.0mm,1,2v2,
TP3,TestPoint_Pad_D1.0mm,1,FPC_3V3_TP,
TP4,TestPoint_Pad_D1.0mm,1,FPC_GND_TP,
"U3, U4",SSOP-24_5.3x8.2mm_P0.65mm,2,CD74HC4067SM,
